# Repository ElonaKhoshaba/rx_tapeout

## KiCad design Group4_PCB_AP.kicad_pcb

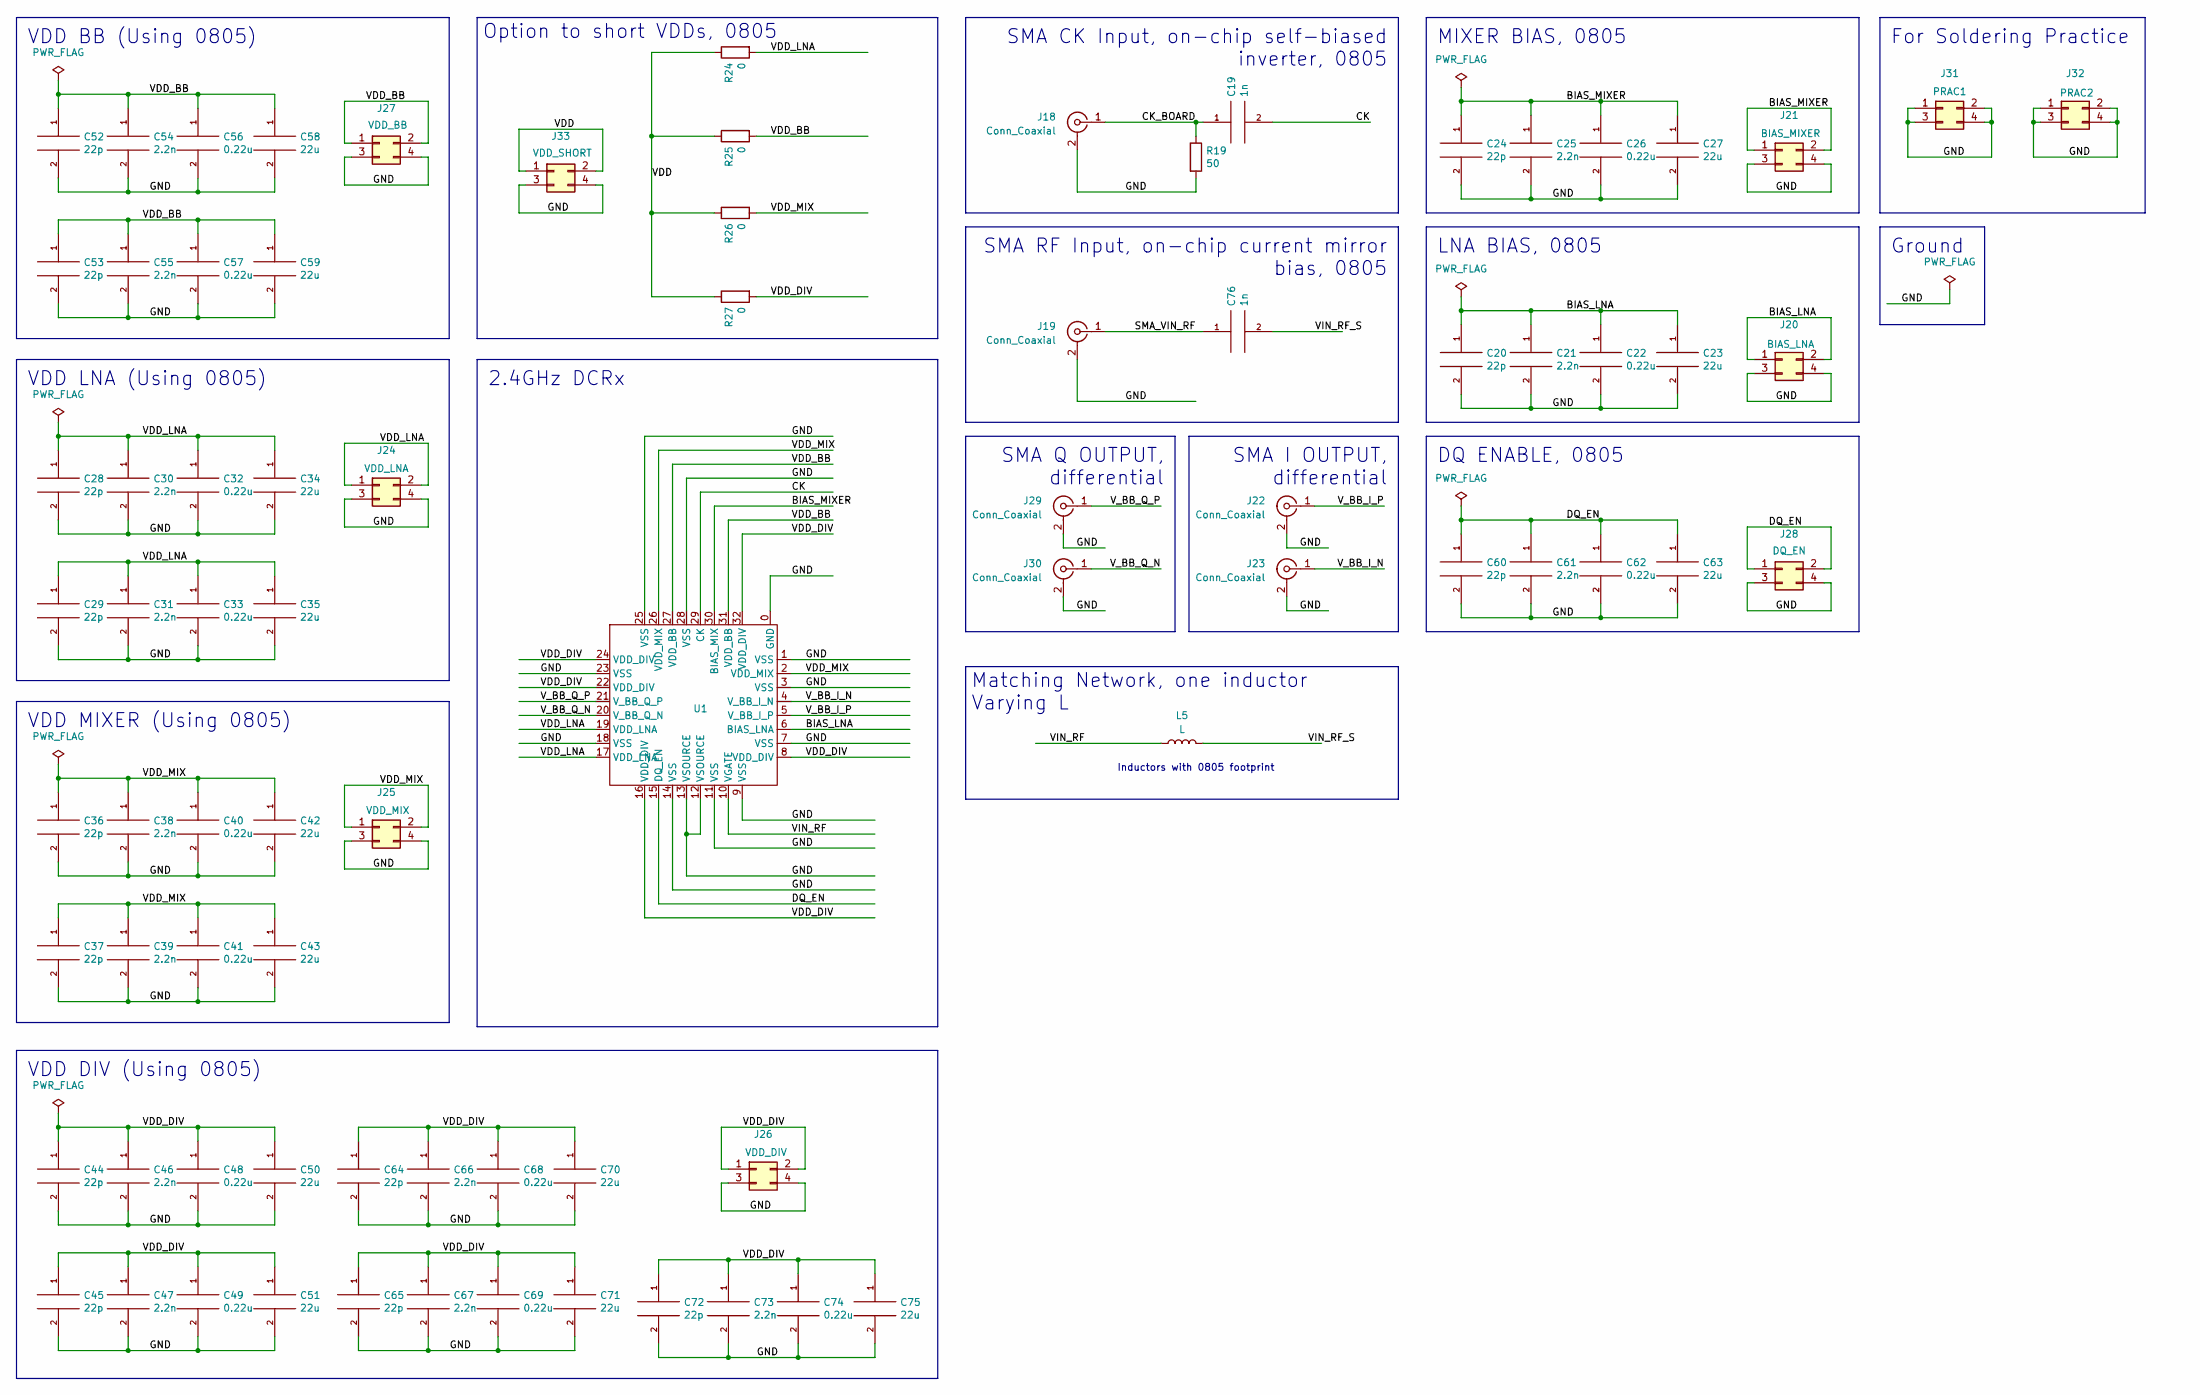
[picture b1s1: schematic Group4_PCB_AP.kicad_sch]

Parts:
C19, C76: 1n; C_0805_2012Metric_Pad1.18x1.45mm_HandSolder; LCSC Part # C46653
C20, C24, C28, C29, C36, C37, C44, C45, C52, C53, C60, C64, C65, C72: 22p; C_0805_2012Metric_Pad1.18x1.45mm_HandSolder; LCSC Part # C1804
C21, C25, C30, C31, C38, C39, C46, C47, C54, C55, C61, C66, C67, C73: 2.2n; C_0805_2012Metric_Pad1.18x1.45mm_HandSolder; LCSC Part # C28260
C22, C26, C32, C33, C40, C41, C48, C49, C56, C57, C62, C68, C69, C74: 0.22u; C_0805_2012Metric_Pad1.18x1.45mm_HandSolder; LCSC Part # C5378
C23, C27, C34, C35, C42, C43, C50, C51, C58, C59, C63, C70, C71, C75: 22u; C_0805_2012Metric_Pad1.18x1.45mm_HandSolder; LCSC Part # C45783
J18, J19, J22, J23, J29, J30: Conn_Coaxial; SMA_Samtec_SMA-J-P-H-ST-EM1_EdgeMount
J20, J21, J24, J25, J26, J27, J28, J31, J32, J33: Conn_02x02_Odd_Even; PinHeader_2x02_P2.54mm_Vertical
L5: L; L_0805_2012Metric_Pad1.15x1.40mm_HandSolder
R19: 50; R_0805_2012Metric_Pad1.20x1.40mm_HandSolder
R24, R25, R26, R27: 0; R_0805_2012Metric_Pad1.20x1.40mm_HandSolder; LCSC Part # C17738
U1: CCJ04403

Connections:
/BIAS_LNA: C20.1, C21.1, C22.1, C23.1, J20.1, J20.2, U1.6 (BIAS_LNA)
/BIAS_MIXER: C24.1, C25.1, C26.1, C27.1, J21.1, J21.2, U1.30 (BIAS_MIX)
/CK: C19.2, U1.29 (CK)
/CK_BOARD: C19.1, J18.1 (In), R19.1
/DQ_EN: C60.1, C61.1, C62.1, C63.1, J28.1, J28.2, U1.15 (DQ_EN)
/GND: C20.2, C21.2, C22.2, C23.2, C24.2, C25.2, C26.2, C27.2, C28.2, C29.2, C30.2, C31.2, C32.2, C33.2, C34.2, C35.2, C36.2, C37.2, C38.2, C39.2, C40.2, C41.2, C42.2, C43.2, C44.2, C45.2, C46.2, C47.2, C48.2, C49.2, C50.2, C51.2, C52.2, C53.2, C54.2, C55.2, C56.2, C57.2, C58.2, C59.2, C60.2, C61.2, C62.2, C63.2, C64.2, C65.2, C66.2, C67.2, C68.2, C69.2, C70.2, C71.2, C72.2, C73.2, C74.2, C75.2, J18.2 (Ext), J19.2 (Ext), J20.3, J20.4, J21.3, J21.4, J22.2 (Ext), J23.2 (Ext), J24.3, J24.4, J25.3, J25.4, J26.3, J26.4, J27.3, J27.4, J28.3, J28.4, J29.2 (Ext), J30.2 (Ext), J31.1, J31.2, J31.3, J31.4, J32.1, J32.2, J32.3, J32.4, J33.3, J33.4, R19.2, U1.0 (GND), U1.1 (VSS), U1.3 (VSS), U1.7 (VSS), U1.9 (VSS), U1.11 (VSS), U1.12 (VSOURCE), U1.13 (VSOURCE), U1.14 (VSS), U1.18 (VSS), U1.23 (VSS), U1.25 (VSS), U1.28 (VSS)
/SMA_VIN_RF: C76.1, J19.1 (In)
/VDD: J33.1, J33.2, R24.1, R25.1, R26.1, R27.1
/VDD_BB: C52.1, C53.1, C54.1, C55.1, C56.1, C57.1, C58.1, C59.1, J27.1, J27.2, R25.2, U1.27 (VDD_BB), U1.31 (VDD_BB)
/VDD_DIV: C44.1, C45.1, C46.1, C47.1, C48.1, C49.1, C50.1, C51.1, C64.1, C65.1, C66.1, C67.1, C68.1, C69.1, C70.1, C71.1, C72.1, C73.1, C74.1, C75.1, J26.1, J26.2, R27.2, U1.8 (VDD_DIV), U1.16 (VDD_DIV), U1.22 (VDD_DIV), U1.24 (VDD_DIV), U1.32 (VDD_DIV)
/VDD_LNA: C28.1, C29.1, C30.1, C31.1, C32.1, C33.1, C34.1, C35.1, J24.1, J24.2, R24.2, U1.17 (VDD_LNA), U1.19 (VDD_LNA)
/VDD_MIX: C36.1, C37.1, C38.1, C39.1, C40.1, C41.1, C42.1, C43.1, J25.1, J25.2, R26.2, U1.2 (VDD_MIX), U1.26 (VDD_MIX)
/VIN_RF: L5.2, U1.10 (VGATE)
/VIN_RF_S: C76.2, L5.1
/V_BB_I_N: J23.1 (In), U1.4 (V_BB_I_N)
/V_BB_I_P: J22.1 (In), U1.5 (V_BB_I_P)
/V_BB_Q_N: J30.1 (In), U1.20 (V_BB_Q_N)
/V_BB_Q_P: J29.1 (In), U1.21 (V_BB_Q_P)

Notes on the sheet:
Inductors with 0805 footprint
DQ ENABLE, 0805
VDD DIV (Using 0805)
SMA CK Input, on-chip self-biased inverter, 0805
Ground
2.4GHz DCRx
VDD BB (Using 0805)
VDD MIXER (Using 0805)
SMA I OUTPUT, differential
LNA BIAS, 0805
SMA Q OUTPUT, differential
Option to short VDDs, 0805
VDD LNA (Using 0805)
SMA RF Input, on-chip current mirror bias, 0805
Matching Network, one inductor Varying L
MIXER BIAS, 0805
For Soldering Practice

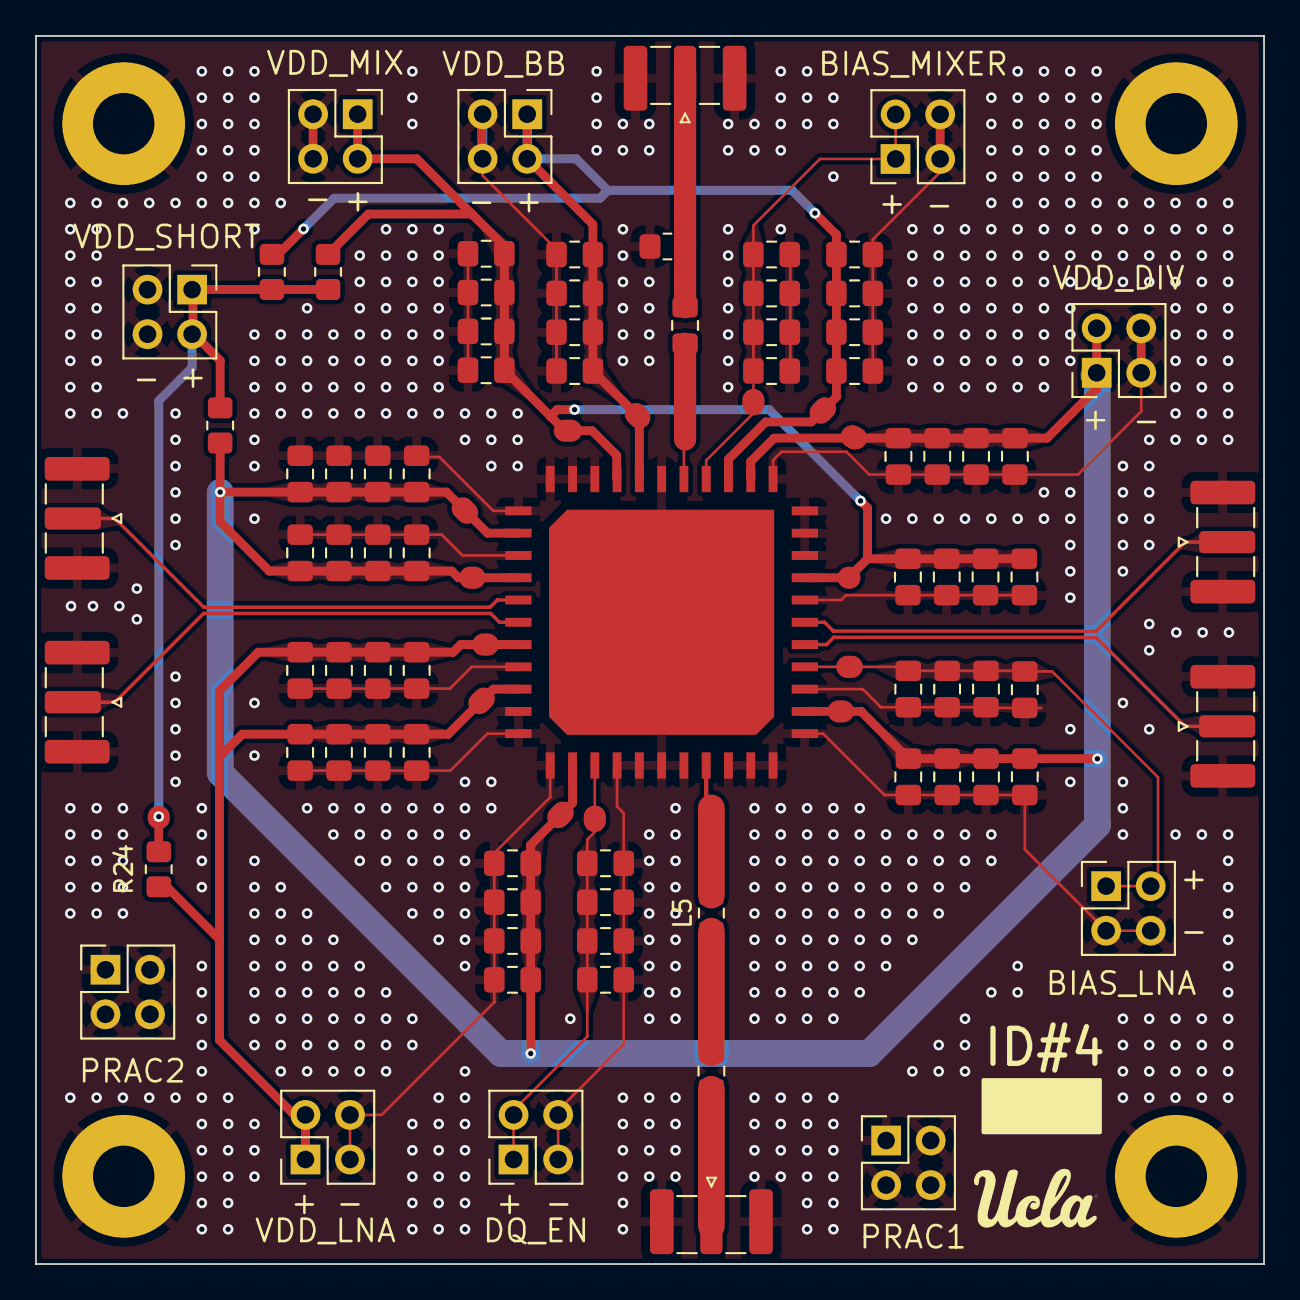
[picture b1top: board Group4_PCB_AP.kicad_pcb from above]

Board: 2 copper layers, 70.0 x 70.0 mm, 81 parts (0 on the bottom side), 18 nets.

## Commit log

2025-08-17 Creating PCB copy in layout
    Created PCB layout and tied all the components to the respective components in schematic view.
2025-08-24 Reorganized layout
    Reorganized layout and updated nets and chip symbol to reflect proper pinout
2025-08-25 Started routing
    Routed almost all nets. Need to finish routing VDD_DIV, GND pour, and matching network
2025-08-27 Finished Routing
    At 1:35 in video. Finished routing everything. Need to add probe points, via stitching, ID marker, matching network
2025-08-28 Additions to schematic and layout
    Added coupling cap for RF input
    Added matching network with zero ohm resistors to detach it
    Added zero ohm resistors to VDD lines.
    Need to add probe points, via stitches, and ID
2025-08-28 updated matching nw, added probe points, via stitching. TODO: fix DRC errors
2025-08-28 Added probe point to bias_mixer
    As title says
2025-08-29 Cleaned up matching network
    Cleaned up schematic and layout for matching network, removed termination and 0 ohm resistors, removed probe points on all RF traces. Removed zero ohm from VSOURCE
2025-09-01 fixed up some caps, 4mm away from chip. need to check if the adjcaent caps r too close
2025-09-07 finished rerouting
2025-09-07 fixed DRC except ONE; added via stitching; need to do test points
2025-09-08 Fixed final DRC error
    DRC clean and added probe points
2025-09-10 Added UCLA Silk Screen and Gerber files
    Finalized PCB and made Gerber files
